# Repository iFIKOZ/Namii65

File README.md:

# Namii65
 Open-Source Mechanical Keyboard PCB with 65% layout and using ProMicro as main MCU

# Layout
* 65%
* 2 Bottom Row (Ansi and Tsangan)
* Stepped Capslock

# Firmware
Not Uploaded yet

# Info
This is the v2 of the pcb

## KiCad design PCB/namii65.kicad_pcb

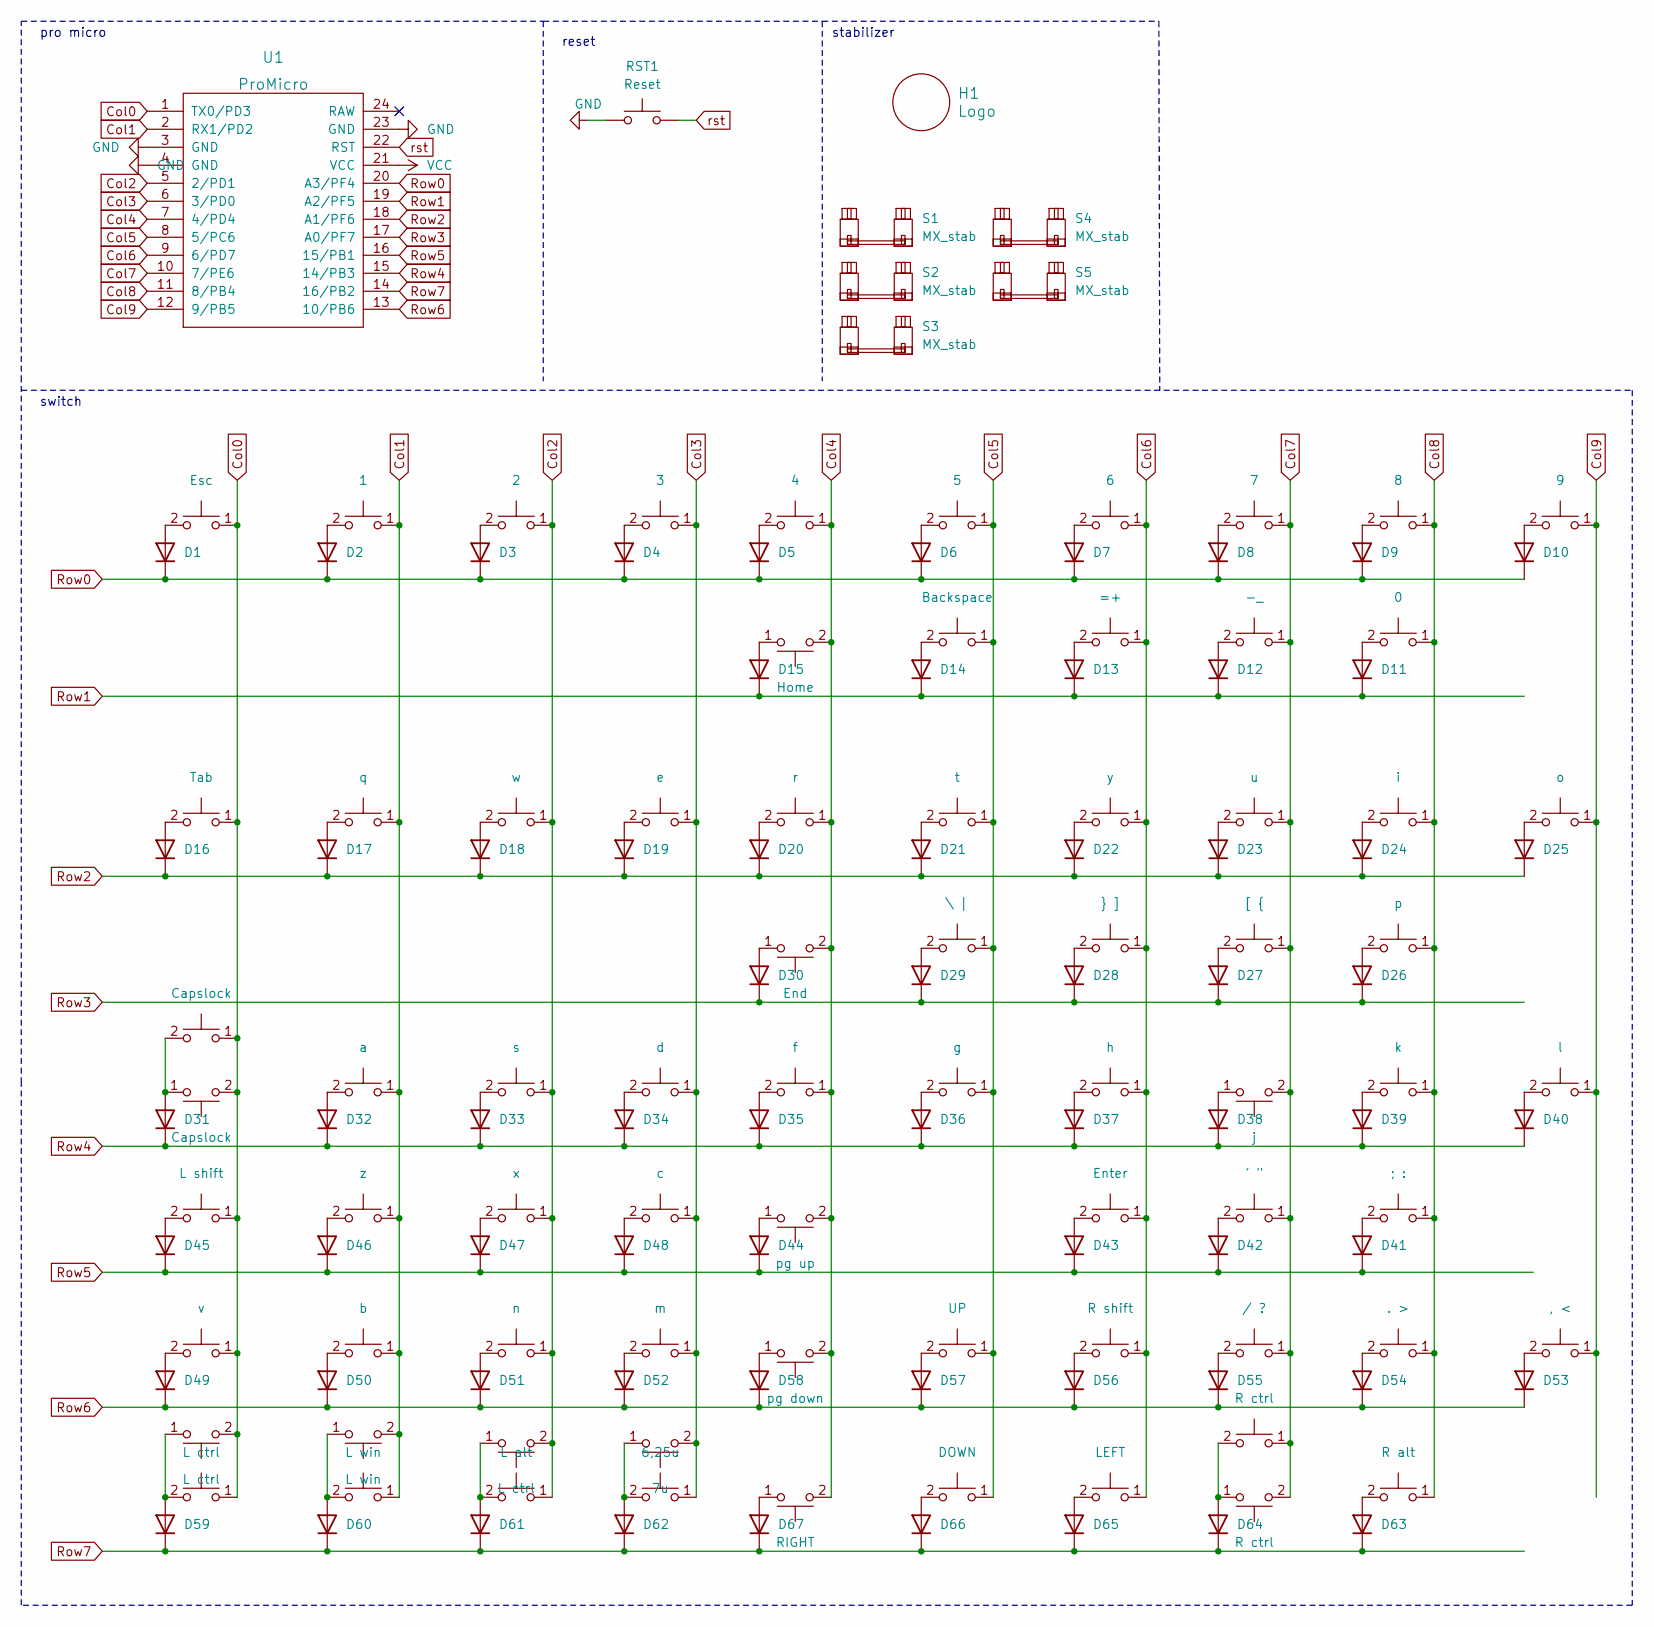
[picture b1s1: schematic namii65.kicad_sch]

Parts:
D1, D2, D3, D4, D5, D6, D7, D8, D9, D10, D11, D12, D13, D14, D15, D16, D17, D18, D19, D20, D21, D22, D23, D24, D25, D26, D27, D28, D29, D30, D31, D32, D33, D34, D35, D36, D37, D38, D39, D40, D41, D42, D43, D44, D45, D46, D47, D48, D49, D50, D51, D52, D53, D54, D55, D56, D57, D58, D59, D60, D61, D62, D63, D64, D65, D66, D67: 1N4148W; D_SOD123
H1: Logo; FIKOZ_logo_1
RST1: Reset; PinHeader_1x02_P2.54mm_Vertical
S1, S2, S3: MX_stab; Stabilizer_Cherry_MX_2.00u
S4: MX_stab; Stabilizer_Cherry_MX_6.25u
S5: MX_stab; Stabilizer_Cherry_MX_7.00u
SW1: Esc; SW_Hotswap_Kailh_MX_1.00u
SW2: 1; SW_Hotswap_Kailh_MX_1.00u
SW3: 2; SW_Hotswap_Kailh_MX_1.00u
SW4: 3; SW_Hotswap_Kailh_MX_1.00u
SW5: 4; SW_Hotswap_Kailh_MX_1.00u
SW6: 5; SW_Hotswap_Kailh_MX_1.00u
SW7: 6; SW_Hotswap_Kailh_MX_1.00u
SW8: 7; SW_Hotswap_Kailh_MX_1.00u
SW9: 8; SW_Hotswap_Kailh_MX_1.00u
SW10: 9; SW_Hotswap_Kailh_MX_1.00u
SW11: 0; SW_Hotswap_Kailh_MX_1.00u
SW12: -_; SW_Hotswap_Kailh_MX_1.00u
SW13: =+; SW_Hotswap_Kailh_MX_1.00u
SW14: Backspace; SW_Hotswap_Kailh_MX_1.00u
SW15: Home; SW_Hotswap_Kailh_MX_1.00u
SW16: Tab; SW_Hotswap_Kailh_MX_1.00u
SW17: q; SW_Hotswap_Kailh_MX_1.00u
SW18: w; SW_Hotswap_Kailh_MX_1.00u
SW19: e; SW_Hotswap_Kailh_MX_1.00u
SW20: r; SW_Hotswap_Kailh_MX_1.00u
SW21: t; SW_Hotswap_Kailh_MX_1.00u
SW22: y; SW_Hotswap_Kailh_MX_1.00u
SW23: u; SW_Hotswap_Kailh_MX_1.00u
SW24: i; SW_Hotswap_Kailh_MX_1.00u
SW25: o; SW_Hotswap_Kailh_MX_1.00u
SW26: p; SW_Hotswap_Kailh_MX_1.00u
SW27: [ {; SW_Hotswap_Kailh_MX_1.00u
SW28: } ]; SW_Hotswap_Kailh_MX_1.00u
SW29: \ |; SW_Hotswap_Kailh_MX_1.00u
SW30: End; SW_Hotswap_Kailh_MX_1.00u
SW31: Capslock; SW_Hotswap_Kailh_MX_1.75u
SW32: a; SW_Hotswap_Kailh_MX_1.00u
SW33: s; SW_Hotswap_Kailh_MX_1.00u
SW34: d; SW_Hotswap_Kailh_MX_1.00u
SW35: f; SW_Hotswap_Kailh_MX_1.00u
SW36: g; SW_Hotswap_Kailh_MX_1.00u
SW37: h; SW_Hotswap_Kailh_MX_1.00u
SW38: j; SW_Hotswap_Kailh_MX_1.00u
SW39: k; SW_Hotswap_Kailh_MX_1.00u
SW40: l; SW_Hotswap_Kailh_MX_1.00u
SW41: ; :; SW_Hotswap_Kailh_MX_1.00u
SW42: ' "; SW_Hotswap_Kailh_MX_1.00u
SW43: Enter; SW_Hotswap_Kailh_MX_1.00u
SW44: pg up; SW_Hotswap_Kailh_MX_1.00u
SW45: L shift; SW_Hotswap_Kailh_MX_1.00u
SW46: z; SW_Hotswap_Kailh_MX_1.00u
SW47: x; SW_Hotswap_Kailh_MX_1.00u
SW48: c; SW_Hotswap_Kailh_MX_1.00u
SW49: v; SW_Hotswap_Kailh_MX_1.00u
SW50: b; SW_Hotswap_Kailh_MX_1.00u
SW51: n; SW_Hotswap_Kailh_MX_1.00u
SW52: m; SW_Hotswap_Kailh_MX_1.00u
SW53: , <; SW_Hotswap_Kailh_MX_1.00u
SW54: . >; SW_Hotswap_Kailh_MX_1.00u
SW55: / ?; SW_Hotswap_Kailh_MX_1.00u
SW56: R shift; SW_Hotswap_Kailh_MX_1.00u
SW57: UP; SW_Hotswap_Kailh_MX_1.00u
SW58: pg down; SW_Hotswap_Kailh_MX_1.00u
SW59: L ctrl; SW_Hotswap_Kailh_MX_1.25u
SW60, SW69: L win; SW_Hotswap_Kailh_MX_1.00u
SW61: L alt; SW_Hotswap_Kailh_MX_1.00u
SW62: 6,25u; SW_Hotswap_Kailh_MX_1.00u
SW63: R alt; SW_Hotswap_Kailh_MX_1.00u
SW64: R ctrl; SW_Hotswap_Kailh_MX_1.00u
SW65: LEFT; SW_Hotswap_Kailh_MX_1.00u
SW66: DOWN; SW_Hotswap_Kailh_MX_1.00u
SW67: RIGHT; SW_Hotswap_Kailh_MX_1.00u
SW68, SW70: L ctrl; SW_Hotswap_Kailh_MX_1.50u
SW71: 7u; SW_Hotswap_Kailh_MX_7.00u
SW72: R ctrl; SW_Hotswap_Kailh_MX_1.50u
SW73: Capslock; SW_Hotswap_Kailh_MX_1.25u
U1: ProMicro; ProMicro-NoSilk

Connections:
Col0: SW1.1, SW16.1, SW31.2, SW45.1, SW49.1, SW59.1, SW68.2, SW73.1, U1.1 (TX0/PD3)
Col1: SW2.1, SW17.1, SW32.1, SW46.1, SW50.1, SW60.1, SW69.2, U1.2 (RX1/PD2)
Col2: SW3.1, SW18.1, SW33.1, SW47.1, SW51.1, SW61.1, SW70.2, U1.5 (2/PD1)
Col3: SW4.1, SW19.1, SW34.1, SW48.1, SW52.1, SW62.1, SW71.2, U1.6 (3/PD0)
Col4: SW5.1, SW15.2, SW20.1, SW30.2, SW35.1, SW44.2, SW58.2, SW67.2, U1.7 (4/PD4)
Col5: SW6.1, SW14.1, SW21.1, SW29.1, SW36.1, SW57.1, SW66.1, U1.8 (5/PC6)
Col6: SW7.1, SW13.1, SW22.1, SW28.1, SW37.1, SW43.1, SW56.1, SW65.1, U1.9 (6/PD7)
Col7: SW8.1, SW12.1, SW23.1, SW27.1, SW38.2, SW42.1, SW55.1, SW64.2, SW72.1, U1.10 (7/PE6)
Col8: SW9.1, SW11.1, SW24.1, SW26.1, SW39.1, SW41.1, SW54.1, SW63.1, U1.11 (8/PB4)
Col9: SW10.1, SW25.1, SW40.1, SW53.1, U1.12 (9/PB5)
GND: RST1.1, U1.3 (GND), U1.4 (GND), U1.23 (GND)
unnamed: D1.2 (A), SW1.2
unnamed: D2.2 (A), SW2.2
unnamed: D3.2 (A), SW3.2
unnamed: D4.2 (A), SW4.2
unnamed: D5.2 (A), SW5.2
unnamed: D6.2 (A), SW6.2
unnamed: D7.2 (A), SW7.2
unnamed: D8.2 (A), SW8.2
unnamed: D9.2 (A), SW9.2
unnamed: D10.2 (A), SW10.2
unnamed: D11.2 (A), SW11.2
unnamed: D12.2 (A), SW12.2
unnamed: D13.2 (A), SW13.2
unnamed: D14.2 (A), SW14.2
unnamed: D15.2 (A), SW15.1
unnamed: D16.2 (A), SW16.2
unnamed: D17.2 (A), SW17.2
unnamed: D18.2 (A), SW18.2
unnamed: D19.2 (A), SW19.2
unnamed: D20.2 (A), SW20.2
unnamed: D21.2 (A), SW21.2
unnamed: D22.2 (A), SW22.2
unnamed: D23.2 (A), SW23.2
unnamed: D24.2 (A), SW24.2
unnamed: D25.2 (A), SW25.2
unnamed: D26.2 (A), SW26.2
unnamed: D27.2 (A), SW27.2
unnamed: D28.2 (A), SW28.2
unnamed: D29.2 (A), SW29.2
unnamed: D30.2 (A), SW30.1
unnamed: D31.2 (A), SW31.1, SW73.2
unnamed: D32.2 (A), SW32.2
unnamed: D33.2 (A), SW33.2
unnamed: D34.2 (A), SW34.2
unnamed: D35.2 (A), SW35.2
unnamed: D36.2 (A), SW36.2
unnamed: D37.2 (A), SW37.2
unnamed: D38.2 (A), SW38.1
unnamed: D39.2 (A), SW39.2
unnamed: D40.2 (A), SW40.2
unnamed: D41.2 (A), SW41.2
unnamed: D42.2 (A), SW42.2
unnamed: D43.2 (A), SW43.2
unnamed: D44.2 (A), SW44.1
unnamed: D45.2 (A), SW45.2
unnamed: D46.2 (A), SW46.2
unnamed: D47.2 (A), SW47.2
unnamed: D48.2 (A), SW48.2
unnamed: D49.2 (A), SW49.2
unnamed: D50.2 (A), SW50.2
unnamed: D51.2 (A), SW51.2
unnamed: D52.2 (A), SW52.2
unnamed: D53.2 (A), SW53.2
unnamed: D54.2 (A), SW54.2
unnamed: D55.2 (A), SW55.2
unnamed: D56.2 (A), SW56.2
unnamed: D57.2 (A), SW57.2
unnamed: D58.2 (A), SW58.1
unnamed: D59.2 (A), SW59.2, SW68.1
unnamed: D60.2 (A), SW60.2, SW69.1
unnamed: D61.2 (A), SW61.2, SW70.1
unnamed: D62.2 (A), SW62.2, SW71.1
unnamed: D63.2 (A), SW63.2
unnamed: D64.2 (A), SW64.1, SW72.2
unnamed: D65.2 (A), SW65.2
unnamed: D66.2 (A), SW66.2
unnamed: D67.2 (A), SW67.1
Row0: D1.1 (K), D2.1 (K), D3.1 (K), D4.1 (K), D5.1 (K), D6.1 (K), D7.1 (K), D8.1 (K), D9.1 (K), D10.1 (K), U1.20 (A3/PF4)
Row1: D11.1 (K), D12.1 (K), D13.1 (K), D14.1 (K), D15.1 (K), U1.19 (A2/PF5)
Row2: D16.1 (K), D17.1 (K), D18.1 (K), D19.1 (K), D20.1 (K), D21.1 (K), D22.1 (K), D23.1 (K), D24.1 (K), D25.1 (K), U1.18 (A1/PF6)
Row3: D26.1 (K), D27.1 (K), D28.1 (K), D29.1 (K), D30.1 (K), U1.17 (A0/PF7)
Row4: D31.1 (K), D32.1 (K), D33.1 (K), D34.1 (K), D35.1 (K), D36.1 (K), D37.1 (K), D38.1 (K), D39.1 (K), D40.1 (K), U1.15 (14/PB3)
Row5: D41.1 (K), D42.1 (K), D43.1 (K), D44.1 (K), D45.1 (K), D46.1 (K), D47.1 (K), D48.1 (K), U1.16 (15/PB1)
Row6: D49.1 (K), D50.1 (K), D51.1 (K), D52.1 (K), D53.1 (K), D54.1 (K), D55.1 (K), D56.1 (K), D57.1 (K), D58.1 (K), U1.13 (10/PB6)
Row7: D59.1 (K), D60.1 (K), D61.1 (K), D62.1 (K), D63.1 (K), D64.1 (K), D65.1 (K), D66.1 (K), D67.1 (K), U1.14 (16/PB2)
VCC: U1.21 (VCC)
rst: RST1.2, U1.22 (RST)

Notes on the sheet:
reset
pro micro
stabilizer
switch

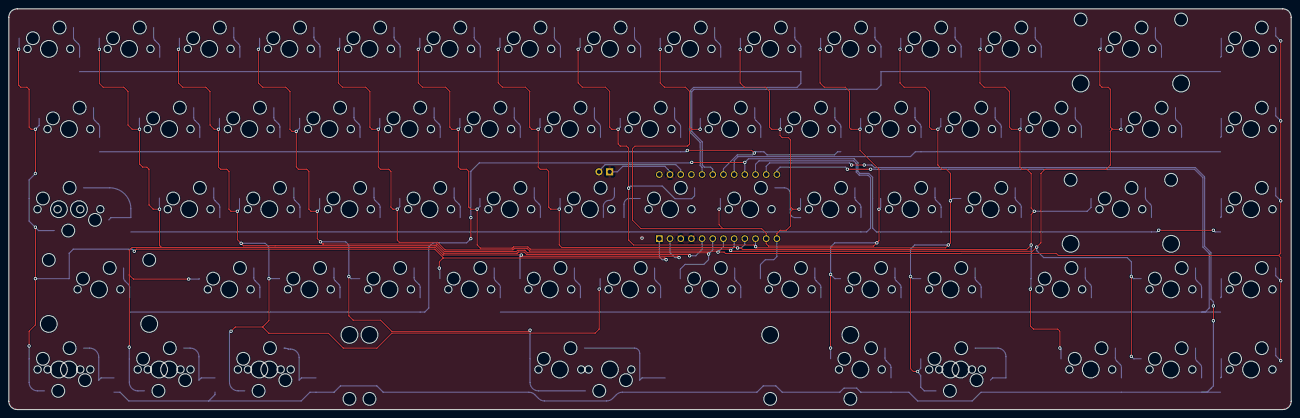
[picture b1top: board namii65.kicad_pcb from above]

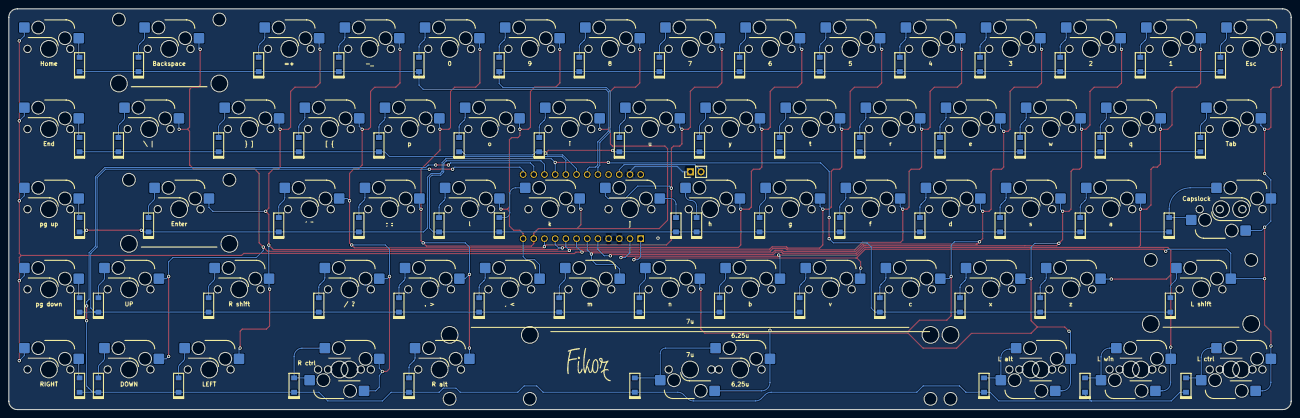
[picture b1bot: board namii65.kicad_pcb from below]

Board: 2 copper layers, 304.8 x 95.2 mm, 148 parts (69 on the bottom side), 87 nets.

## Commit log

2024-12-10 change file
2024-12-11 adding production file
2024-12-12 kle image
